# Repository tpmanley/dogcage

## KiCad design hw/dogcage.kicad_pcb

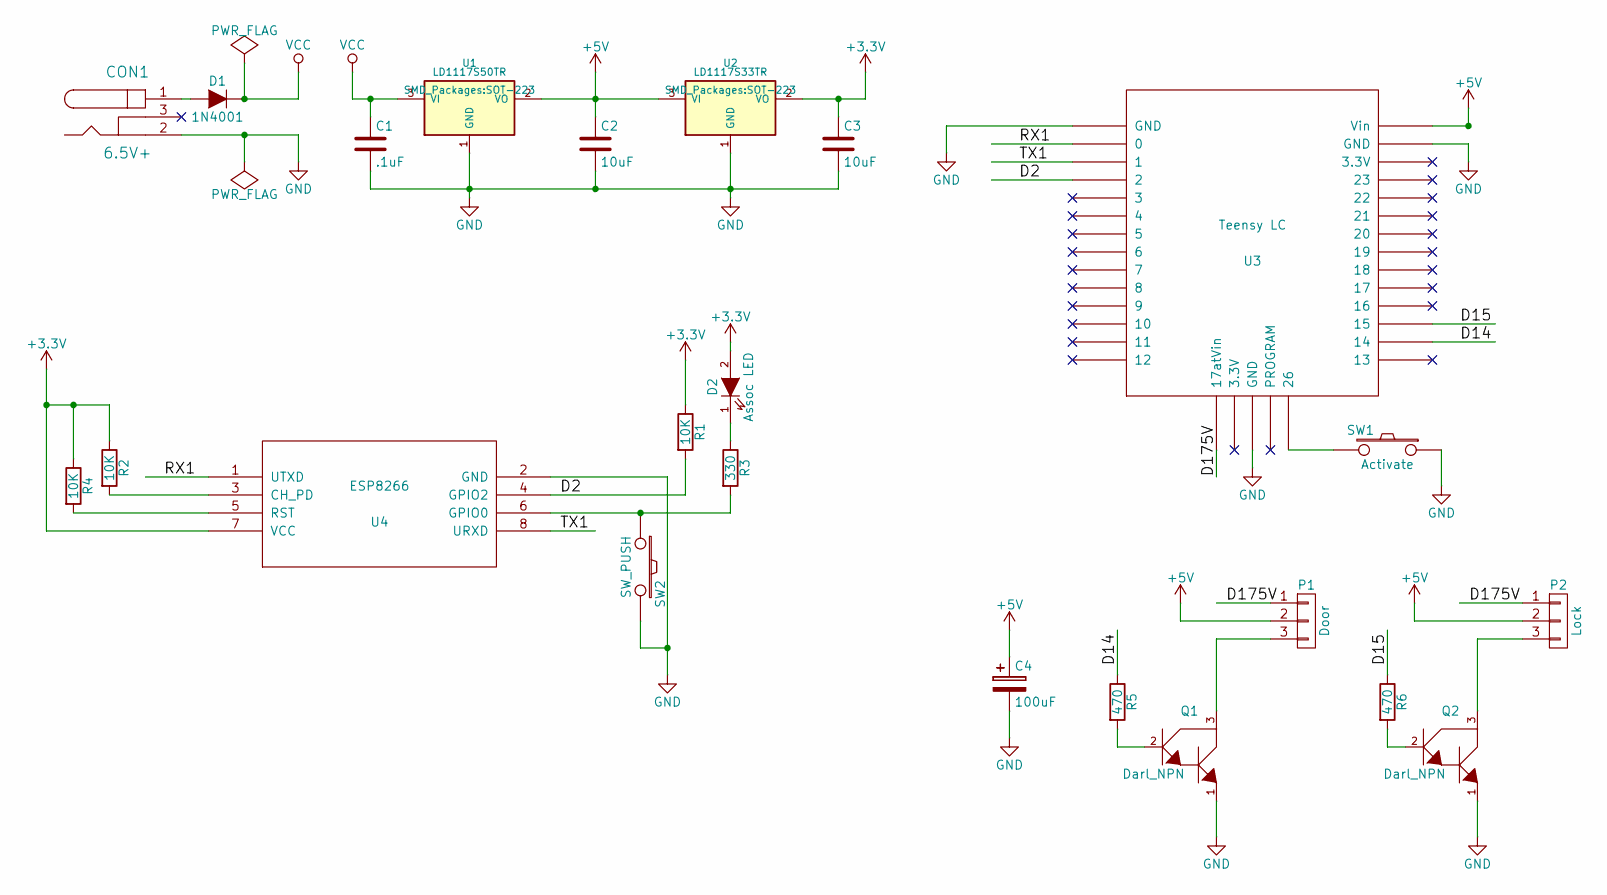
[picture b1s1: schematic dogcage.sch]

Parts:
C1: .1uF; C_0805_HandSoldering
C2, C3: 10uF; C_0805_HandSoldering
C4: 100uF; c_elec_3x5.3
CON1: 6.5V+; BARREL_JACK-ROUND_TH
D1: 1N4001; Diode_DO-41_SOD81_Horizontal_RM10
D2: Assoc LED; LED-0805
P1: Door; Pin_Header_Straight_1x03
P2: Lock; Pin_Header_Straight_1x03
Q1, Q2: Darl_NPN; DPAK-2
R1, R2, R4: 10K; R_0805_HandSoldering
R3: 330; R_0805_HandSoldering
R5, R6: 470; R_0805_HandSoldering
SW1: Activate; SW_PUSH_SMALL
SW2: SW_PUSH; SW_SPST_FSMSM
U1: LD1117S50TR; SOT-223
U2: LD1117S33TR; SOT-223
U3: Teensy LC; Teensy-3.1
U4: ESP8266; ESP-01

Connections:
+3V3: C3.1, D2.2 (A), R1.1, R2.1, R4.1, U2.2 (VO), U4.7 (VCC)
+5V: C2.1, C4.1, P1.2, P2.2, U1.2 (VO), U2.3 (VI), U3.33 (Vin)
/D2: R1.2, U3.4 (2), U4.4 (GPIO2)
/D14: R5.1, U3.21 (14)
/D15: R6.1, U3.22 (15)
/D175V: P1.1, P2.1, U3.15 (17atVin)
/RX1: U3.2 (0), U4.1 (UTXD)
/TX1: U3.3 (1), U4.8 (URXD)
GND: C1.2, C2.2, C3.2, C4.2, CON1.2, Q1.1, Q2.1, SW1.1, SW2.2, U1.1 (GND), U2.1 (GND), U3.1 (GND), U3.17 (GND), U3.32 (GND), U4.2 (GND)
unnamed: CON1.1, D1.2 (A)
unnamed: D2.1 (K), R3.1
unnamed: P1.3, Q1.3
unnamed: P2.3, Q2.3
unnamed: Q1.2, R5.2
unnamed: Q2.2, R6.2
unnamed: R2.2, U4.3 (CH_PD)
unnamed: R3.2, SW2.1, U4.6 (GPIO0)
unnamed: R4.2, U4.5 (RST)
unnamed: SW1.2, U3.19 (26)
VCC: C1.1, D1.1 (K), U1.3 (VI)

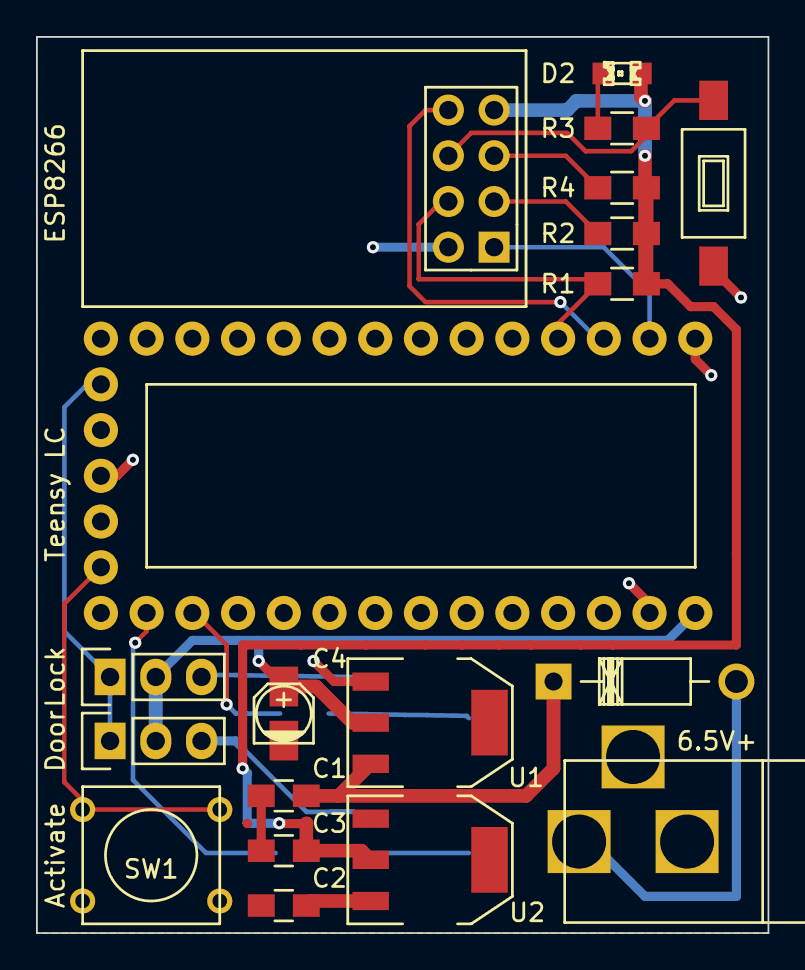
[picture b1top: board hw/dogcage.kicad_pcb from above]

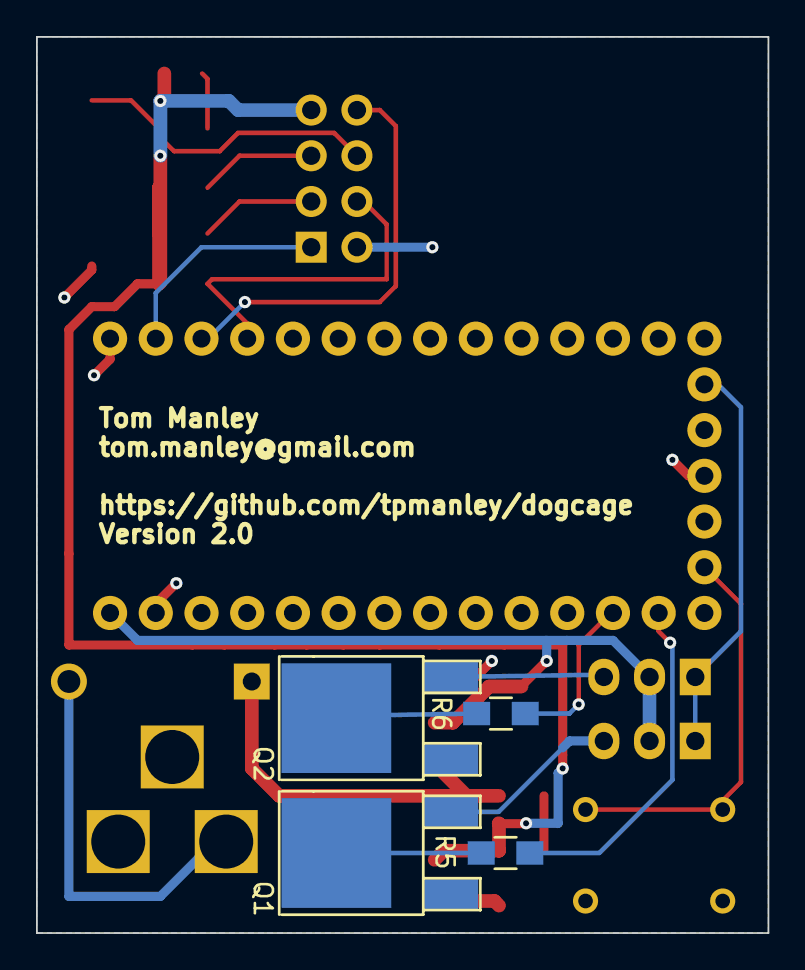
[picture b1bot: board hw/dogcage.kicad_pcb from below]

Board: 2 copper layers, 40.6 x 49.8 mm, 23 parts (4 on the bottom side), 20 nets.

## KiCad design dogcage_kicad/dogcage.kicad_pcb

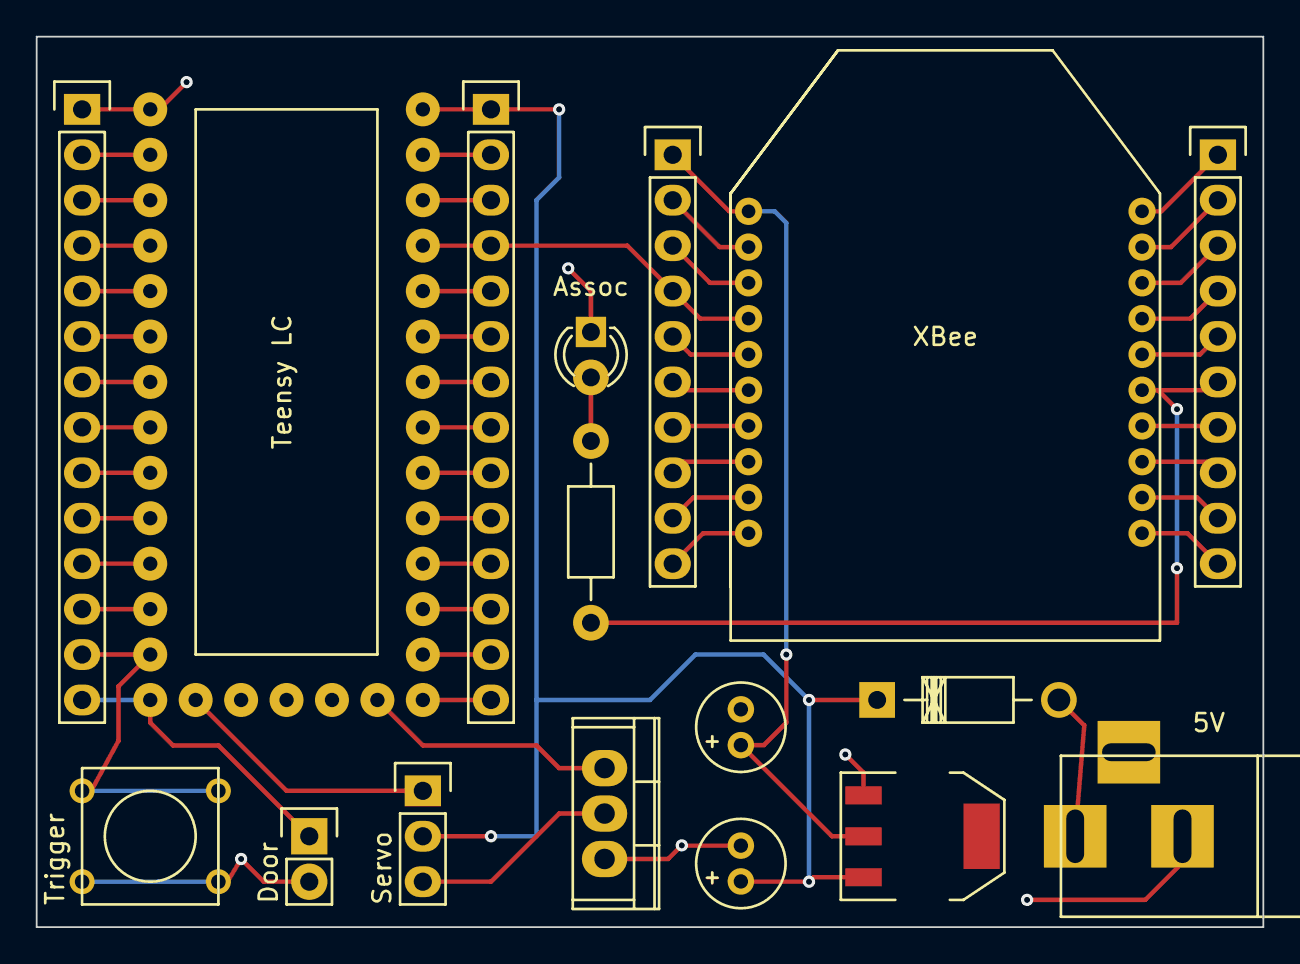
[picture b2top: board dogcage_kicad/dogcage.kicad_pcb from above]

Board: 2 copper layers, 68.6 x 49.8 mm, 17 parts (0 on the bottom side), 51 nets.

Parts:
C1, C2: 10uF; Elko_vert_11x5mm_RM2
CON1: 5V; BARREL_JACK
D1: Assoc; LED-3MM
D2: 1N4001; Diode_DO-41_SOD81_Horizontal_RM10
M1: XBee; xbee
P1: Door; Pin_Header_Straight_1x02
P2: Servo; Pin_Header_Straight_1x03
P3, P4: CONN_01X10; Pin_Header_Straight_1x10
P5, P7: CONN_01X14; Pin_Header_Straight_1x14
Q1: TIP120; TO-220
R1: 330; Resistor_Horizontal_RM10mm
SW1: Trigger; SW_PUSH_SMALL
U1: LD1117S33TR; SOT-223
U2: Teensy LC; Teensy-3.1

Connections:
+3V3: C2.1, M1.1, P3.1, U1.2
+5V: C1.1, D2.1, P2.2, P7.1, U1.3, U2.33
/XBEE_CTL: M1.4, P3.4, P7.4, U2.30
GND: C1.2, C2.2, CON1.2, D1.1, M1.10, P1.2, P3.10, P5.1, Q1.3, SW1.2, U1.1, U2.1
unnamed: CON1.1, D2.2
unnamed: D1.2, R1.2
unnamed: M1.2, P3.2
unnamed: M1.3, P3.3
unnamed: M1.5, P3.5
unnamed: M1.6, P3.6
unnamed: M1.7, P3.7
unnamed: M1.8, P3.8
unnamed: M1.9, P3.9
unnamed: M1.11, P4.10
unnamed: M1.12, P4.9
unnamed: M1.13, P4.8
unnamed: M1.14, P4.7
unnamed: M1.15, P4.6, R1.1
unnamed: M1.16, P4.5
unnamed: M1.17, P4.4
unnamed: M1.18, P4.3
unnamed: M1.19, P4.2
unnamed: M1.20, P4.1
unnamed: P1.1, P5.14, U2.14
unnamed: P2.1, U2.15
unnamed: P2.3, Q1.2
unnamed: P5.2, U2.2
unnamed: P5.3, U2.3
unnamed: P5.4, U2.4
unnamed: P5.5, U2.5
unnamed: P5.6, U2.6
unnamed: P5.7, U2.7
unnamed: P5.8, U2.8
unnamed: P5.9, U2.9
unnamed: P5.10, U2.10
unnamed: P5.11, U2.11
unnamed: P5.12, U2.12
unnamed: P5.13, SW1.1, U2.13
unnamed: P7.2, U2.32
unnamed: P7.3, U2.31
unnamed: P7.5, U2.29
unnamed: P7.6, U2.28
unnamed: P7.7, U2.27
unnamed: P7.8, U2.26
unnamed: P7.9, U2.25
unnamed: P7.10, U2.24
unnamed: P7.11, U2.23
unnamed: P7.12, U2.22
unnamed: P7.13, U2.21
unnamed: P7.14, U2.20
unnamed: Q1.1, U2.19

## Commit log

2015-04-18 Initial commit for arduino powered dog cage opener
2015-04-18 LED will now always blink in loop
2015-04-18 Sucessfully opened cage door
2015-04-19 Close door when DIO is inactive
2015-04-25 Added door open/close sensor
2015-04-25 Significant cleanup and added xbee back in
2015-04-25 Added input test loop
2015-04-26 Button now has pullup and just connects pin to ground
2015-04-26 Added pullup to door sensor which is now connected from pin to ground
2015-04-26 Initial commit of kicad schematic
2015-04-26 Cleaned up schematic and fixed ERC errors
2015-04-26 Added assoc LED and started on PCB
2015-04-30 Add protection diode to input power line
2015-05-02 Added connectors to XBee and Teensy
2015-05-16 Fixed diode orientation and layout WIP
2015-05-16 Fixed cap and resistor footprints, improved overall placement
2015-05-17 Fixed orientation of LED
2015-05-17 Moved XBee control line to make layout easier
2015-05-17 Layout checkpoint
2015-05-19 Routing complete
2015-05-19 Updated design rules for oshpark, getting drc failures on vias
2015-05-22 Fixed drc failure, moved trace out of keep-out zone
2015-05-22 Generated gerbers and drill file
2015-05-22 Fixed front silkscreen, added name/email to back
2015-05-22 Removed P2 from front silkscreen
2015-05-22 Added 'Trigger' to silkscreen
2015-05-23 Sent 1.0 to OSH Park
2015-05-26 Initial commit of servo arm sketchup
2015-05-26 Servo arm now one continguous piece
2015-06-01 First version of doorarm
2015-06-01 Fit in flat servo connector instead of spline
2015-06-03 Arm now engulfs the servo horn
2015-06-04 Updated door arm design to match servo arm design
2015-06-04 Modified for 3d print compatibility. Printed 6-3-15.
2015-06-04 Added rounded end to part that attaches to the cage
2015-06-05 First version of servo mount
2015-06-05 Wrap around entire servo
2015-06-07 Changed screw holes to 1.1mm radius
2015-06-09 Models as printed revision 1.
2015-06-10 Added cutout for wire and increased size of vertical supports
2015-06-11 Fixed ground fill around button
2015-06-11 Reorganized to more sensible repo structure
2015-06-11 Fixed underside polygon mess into a nice plane.
2015-06-12 Renamed sketch to make Arduino IDE happy
2015-06-12 Updated pins to match hw
2015-06-12 Added more support to make servo balance on bar
2015-06-14 Disable door sensor because it isn't working
2015-06-14 Change close position to match position of arm when door is closed
2015-06-14 Renabled XBee signaling
2015-06-18 Bulk cap to 5V and current limiting resistor to TIP120 base
2015-07-11 Added lock servo
2015-07-11 Added 5V regulator to schematic
2015-07-17 Removed XBee, moved bulk cap to be close to servo
2015-07-17 Removed Teensy breakout, still wiring up
2015-07-17 Removed door sensor
2015-07-17 Cleaned up Teensy connections, still getting DRC errors
2015-07-19 Added pwr_flag to GND, fixed DRC failures
2015-07-19 Switched to non-polarized caps on regulators
2015-07-19 Placement in progress
2015-07-25 Swapped TIP120s out for generic Darlington NPN transistors
2015-07-25 Changed NPN and button footprints to SMD
2015-07-26 Moved servo power control GPIOs to other side of the Teensy
2015-07-26 Changed barrel jack footprint to have round througholes
2015-07-26 Placement is essentially done
2015-07-26 Partially routed
2015-07-26 More routing
2015-07-26 Everything connected except GND
2015-08-02 Almost made all GND connections
